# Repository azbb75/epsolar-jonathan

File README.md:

# epever solar display module

The project contains the source code and dashboard website. You can use pre-built binaries or build the source code.

## Downloading pre-build binaries and directly flashing the esp8266 - Recommended for quick firmware updates and Beginners

On windows, download git bash to easily use the esptool once you download it. https://gitforwindows.org/

1. Download the latest pre-build binaries from here: https://bitbucket.org/jonathangoldnauvogt/epever_solar_display/downloads/

2. Extract the zip folder

3. Follow instructions here to download `esptool`: https://github.com/espressif/esptool

4. Put ESP into bootloader mode. Make sure no other serial com port devices are connected to your machine.

5. Open git bash inside the directory where the zip file was extracted by right clicking "Git Bash Here", type 
```bash
esptool.py write_flash 0x000000 firmware.bin 0x300000 spiffs.bin
```
and press enter.

You should see the progress of the firmware downloading. Troubleshoot as necessary using google, or contact customerservice@snektek.com

## Downloading the source code and building 

### Requirements:

1. Download NodeJs from  https://nodejs.org/en/
2. Install `gulp` globally:
```bash
npm install -g gulp
```
3. Install PlatformIO for Visual Studio Code IDE: https://docs.platformio.org/en/latest/ide/pioide.html 
    
    3.1  Install the PIO ESPAsyncTCP Library:  PIO Home -> Libraries -> (search/select ESPAsyncTCP) -> Install

4. Optionally Install PlatformIO Core: https://docs.platformio.org/en/latest/core.html

### Building the source code
The source code is a platform IO project. There are two ways to build and upload the code:

1. Using Visual Studio Code IDE

    1.1 Open the root folder of the project `File -> Open Folder`

    1.2 To Build the code: `Terminal -> Run Task -> PlatformIO:Build`

    1.3 To Upload the code: `Terminal -> Run Task -> PlatformIO:Upload`

    1.4 To Upload the file system image: `Terminal -> Run Task -> PlatformIO:Upload File System Image` 

2. Using Platform IO Core CLI

    2.1 In CLI change directory to the project folder

    2.2 To Build the code: `platformio run`

    2.3 To Upload the code: `platformio run --target upload`

    2.4 To Upload the file system image: `platformio run --target uploadfs `

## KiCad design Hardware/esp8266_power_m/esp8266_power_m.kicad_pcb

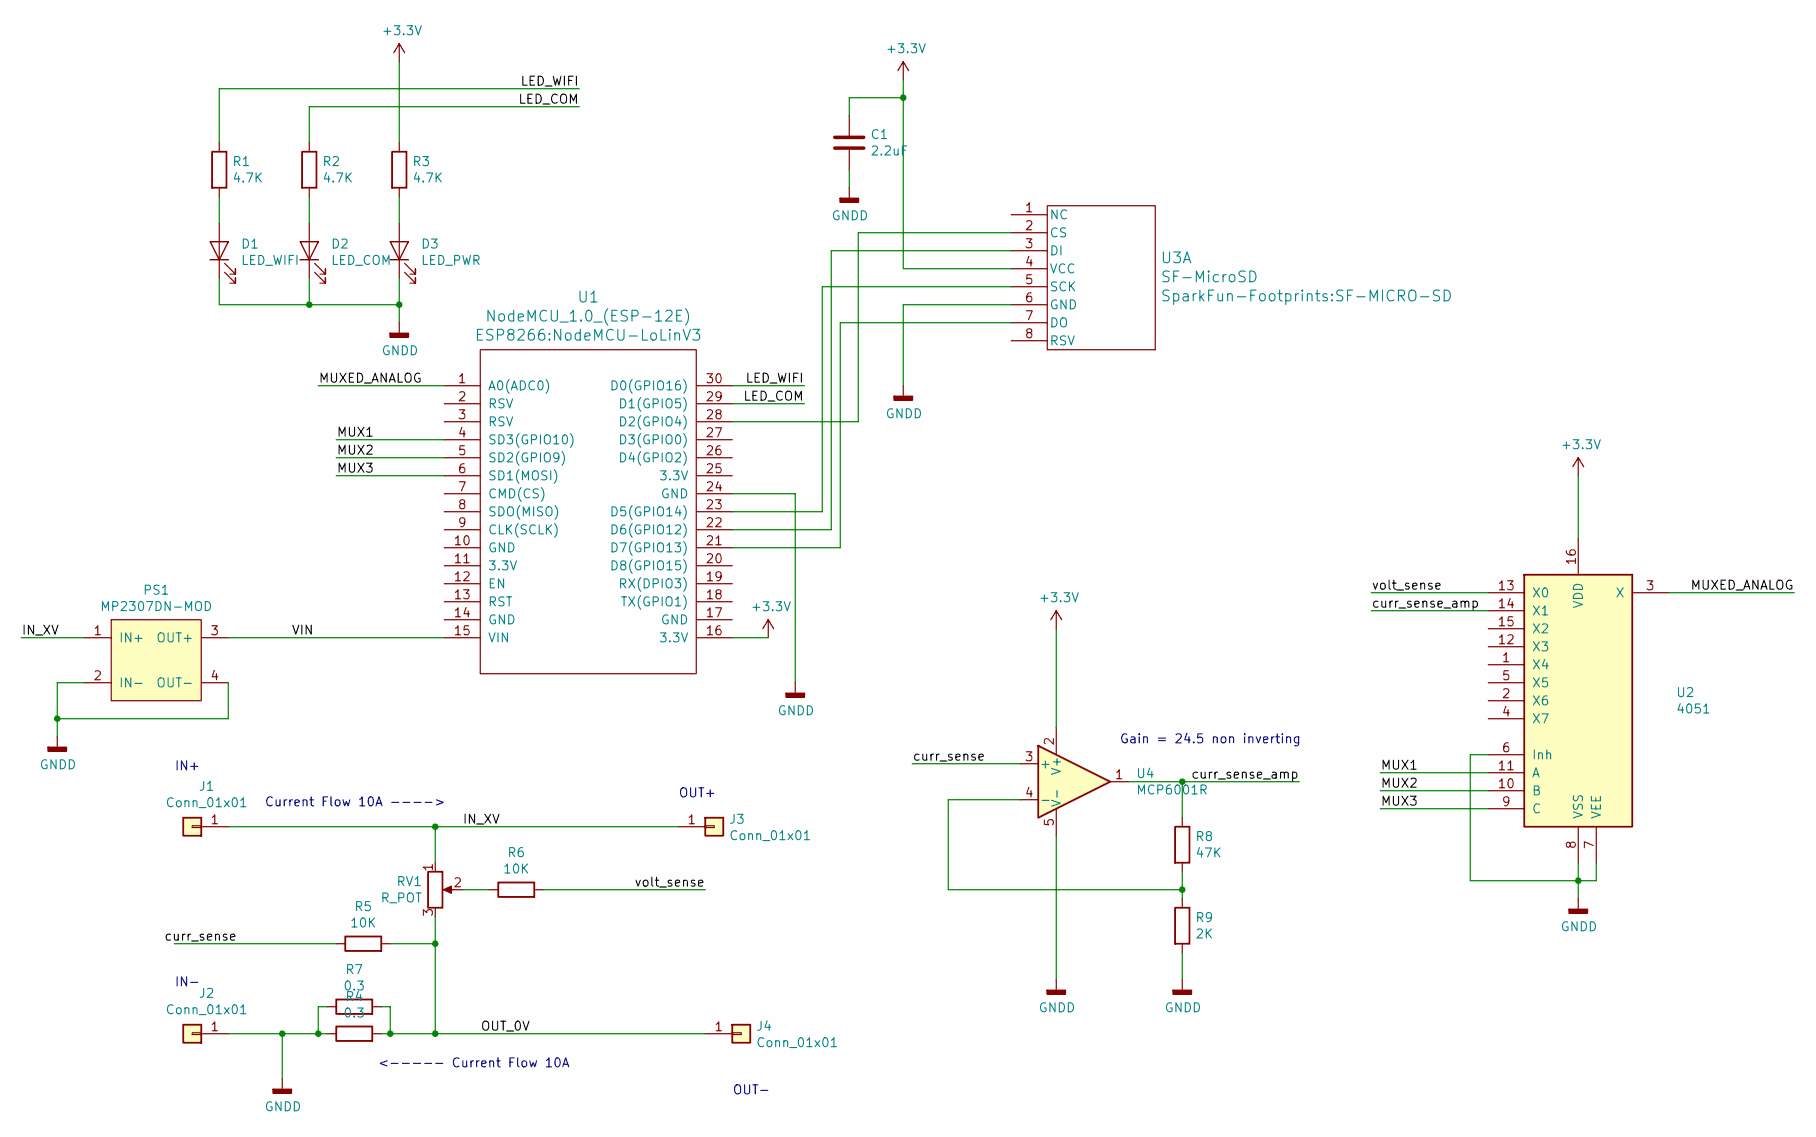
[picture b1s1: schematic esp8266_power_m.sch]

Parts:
C1: 2.2uF; C_0805_2012Metric_Pad1.15x1.40mm_HandSolder
D1: LED_WIFI; LED_D3.0mm
D2: LED_COM; LED_D3.0mm
D3: LED_PWR; LED_D3.0mm
J1, J2, J3, J4: Conn_01x01; TestPoint_THTPad_4.0x4.0mm_Drill2.0mm
PS1: MP2307DN-MOD
R1, R2, R3: 4.7K; R_0805_2012Metric_Pad1.15x1.40mm_HandSolder
R4, R7: 0.3; R_Axial_Power_L20.0mm_W6.4mm_P30.48mm
R5, R6: 10K; R_0805_2012Metric_Pad1.15x1.40mm_HandSolder
R8: 47K; R_0805_2012Metric_Pad1.15x1.40mm_HandSolder
R9: 2K; R_0805_2012Metric_Pad1.15x1.40mm_HandSolder
RV1: R_POT; Potentiometer_Bourns_3314J_Vertical
U1: NodeMCU_1.0_(ESP-12E); NodeMCU-LoLinV3
U2: 4051; SOIC-16_3.9x9.9mm_P1.27mm
U3: SF-MicroSD; SF-MICRO-SD
U4: MCP6001R; SOT-23-5

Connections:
+3V3: C1.1, R3.1, U1.16 (3.3V), U2.16 (VDD), U3.4 (VCC), U4.2 (V+)
/IN_XV: J1.1, J3.1, PS1.1 (IN+), RV1.1
/LED_COM: R2.1, U1.29 (D1(GPIO5))
/LED_WIFI: R1.1, U1.30 (D0(GPIO16))
/MUX1: U1.4 (SD3(GPIO10)), U2.11 (A)
/MUX2: U1.5 (SD2(GPIO9)), U2.10 (B)
/MUX3: U1.6 (SD1(MOSI)), U2.9 (C)
/MUXED_ANALOG: U1.1 (A0(ADC0)), U2.3 (X)
/OUT_0V: J4.1, R4.2, R5.2, R7.2, RV1.3
/VIN: PS1.3 (OUT+), U1.15 (VIN)
/curr_sense: R5.1, U4.3 (+)
/curr_sense_amp: R8.1, U2.14 (X1), U4.1
/volt_sense: R6.2, U2.13 (X0)
GNDD: C1.2, D1.1 (K), D2.1 (K), D3.1 (K), J2.1, PS1.2 (IN-), PS1.4 (OUT-), R4.1, R7.1, R9.2, U1.24 (GND), U2.6 (Inh), U2.7 (VEE), U2.8 (VSS), U3.6 (GND), U4.5 (V-)
unnamed: D1.2 (A), R1.2
unnamed: D2.2 (A), R2.2
unnamed: D3.2 (A), R3.2
unnamed: R6.1, RV1.2
unnamed: R8.2, R9.1, U4.4 (-)
unnamed: U1.21 (D7(GPIO13)), U3.7 (DO)
unnamed: U1.22 (D6(GPIO12)), U3.3 (DI)
unnamed: U1.23 (D5(GPIO14)), U3.5 (SCK)
unnamed: U1.28 (D2(GPIO4)), U3.2 (CS)

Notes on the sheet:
Current Flow 10A ---->
IN+
IN-
<----- Current Flow 10A
OUT-
OUT+
Gain = 24.5 non inverting

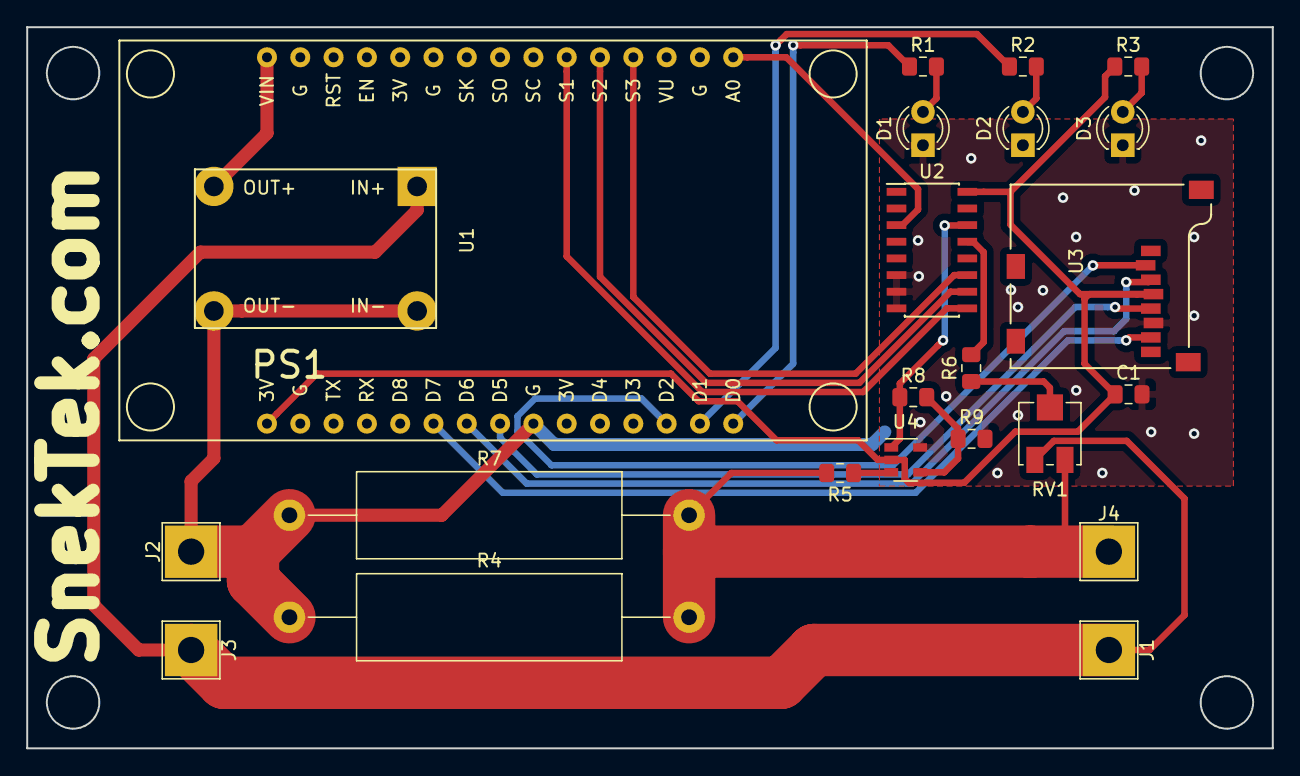
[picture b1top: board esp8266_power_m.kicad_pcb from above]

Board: 2 copper layers, 95.0 x 55.0 mm, 23 parts (0 on the bottom side), 23 nets.
